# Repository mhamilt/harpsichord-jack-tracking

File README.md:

# Harpsichord Jack Tracking

This repository collects together all materials (CAD Drawings, diagrams, firmware source code) related to Harpsichord Jack Tracking Project at the NEMUS project.

|                              |
| :---------------------------------------------------------: |
| Side View of the model harpsichord used during development. |

- [Harpsichord Jack Tracking](#harpsichord-jack-tracking)
  - [Measurements](#measurements)
    - [Model Keyboard](#model-keyboard)
    - [Jack Pitch](#jack-pitch)
    - [Full Scale Keyboard](#full-scale-keyboard)
    - [Jack Pitch](#jack-pitch-1)
    - [Jack Travel](#jack-travel)
    - [PCB](#pcb)
      - [7 Sensor Face Board](#7-sensor-face-board)
        - [Notes](#notes)
        - [Eagle commands](#eagle-commands)
    - [Gradient Tag](#gradient-tag)
    - [Diagram](#diagram)
  - [QRE1113 Notes](#qre1113-notes)
    - [Spacing](#spacing)
    - [Functionality](#functionality)
    - [Data sheets](#data-sheets)
    - [Multiplexing](#multiplexing)
      - [1. Using 2 Micro controllers](#1-using-2-micro-controllers)
  - [MIDI Specifications](#midi-specifications)
    - [Jack Differentiation](#jack-differentiation)
    - [Aftertouch](#aftertouch)

## Measurements

### Model Keyboard

###  Jack Pitch

| Jack | Centre distance from backboard (mm) |
| ---- | ----------------------------------- |
| 1    | `10.25`                             |
| 2    | `25.1`                              |
| 3    | `38.5`                              |

Gives a rough jack pitch of `14.4875 mm` with an offset of `10.25 mm`.

Pitch of the back row of jacks was determined by measuring from the open edge of the model to the front edge of the jack. Each jack had its width measured providing the values in the table below.

| Jack | Front edge dist (mm) | Width (mm) | Centre dist (mm) |
| ---- | -------------------- | ---------- | ---------------- |
| 4    | `59.85`              | `4.25`     | `61.975`         |
| 5    | `45.25`              | `4.30`     | `47.400`         |
| 6    | `31.20`              | `4.60`     | `33.500`         |

Give a rough pitch of `14.2375 mm` with an offset of  `33.5 mm` from the front edge

### Full Scale Keyboard 

|        |
| :-----------------------------: |
| Top view of the 49-key keyboard |ll

The full scale version of the interface has 49 keys and 2 jack rows. The jacks are generally around `4.65 mm`.

###  Jack Pitch

There is not much variation in the pitch of the jacks. On average the centre-to-centre is `14.02 mm`. Likely error between jacks would compound across the full length. This should be compensated for by the separate pcbs which have groups of 7 sensors.

Space between the jacks is `9.75 mm`, meaning central pcbs will have to have less than half this distance (`4.875mm`) in order to slot together.

###  Jack Travel

The jacks have a height of `91.65mm`. Front jacks have a travel of about `8.5mm` and back jacks `9.0mm` between key release and full key press.

### PCB

With a pitch of `14.02 mm` a theoretical limit to the width of a 7-sensor PCB would be `98.2 mm`, but with margin required from traces this is not possible. The upper limit is `112.22 mm` but with variation during fabrication it is unwise to push the tolerance to the nearest `1/10 mm`. A `1.5 mm` tolerance brings the limit to about `99.7 mm` to `110.7 mm`

#### 7 Sensor Face Board

Face boards mount the QRE1113s perpendicular to the board so that there is no need to bend the through hole mounting legs during assembly.

There are a couple of designs, at at present what is most important is the hole mounts at (`18.00mm`, `10.00mm`) and (`18.00mm`, `81.40mm`)

##### Notes

##### Eagle commands

```py
ox = 1.71     # min distance from board edge
pitch = 14.02 # jack pitch
[(x * pitch) + ox for x in range(0,7)]
[1.71, 15.73, 29.75, 43.77, 57.79, 71.80999999999999, 85.83]
```

Python can be used to automatically generate the placement of all pieces.

```py
qrepitch = 1.8 # placement is calculated from the #1 pin, pitch is used to offset to the centre
ox = 1.71     # min distance from board edge
oy = 1.71     # min distance from board edge in y axis
pitch = 14.02 # jack pitch
max_board_width = (6*pitch) + ox + qrepitch + ox

for index, point in enumerate([(x * pitch) + ox for x in range(0,7)]):
  print(f"move Q{index+1} ({oy} {point});")
  # print(f"rotate Q{index+1};")
for index, point in enumerate([(x * pitch) + ox for x in range(0,16)]):
  print(f"move Q{index+1} ({oy} {point});")

# Ideal LED placement
for index, point in enumerate([(x * pitch) + ox for x in range(0,7)]):
  print(f"move D{index+1} ({23.8} {point+qrepitch/2});")

resitor10k_ox = 10.1 # min distance from board edge in y axis
resitor10k_oy = 7.0 # min distance from board edge in y axis
resitor100_ox = 7.5 # min distance from board edge in y axis
resitor100_oy = 7.0 # min distance from board edge in y axis
rpitch = 12.9

for index, point in enumerate([(x * rpitch) + resitor100_oy for x in range(0,16)]):
  if index < 7:
    print(f"move R{(index*2)+1} ({resitor100_ox} {point});")
    print(f"move R{(index+1)*2} ({resitor10k_ox} {point});")
  if index >= 7:
    print(f"move R{((index+1)*2)+1} ({resitor100_ox} {point});")
    print(f"move R{((index+1)+1)*2} ({resitor10k_ox} {point});")

for index, point in enumerate([(x * 12.6) + 7 for x in range(0,7)]):
  print(f"move LED{(index+1)} (34 {point});")

for index, point in enumerate([(x * 12.) + 7 for x in range(0,7)]):
  print(f"rotate LED{(index+1)};")

for index, point in enumerate([(x * 12.6) + 7 for x in range(17,34)]):
  print(f"rotate R{(index+17)};")

for index, point in enumerate([(x * 12.6) + 7 for x in range(0,7)]):
  print(f"rotate R{(index+15)};")
  print(f"move R{(index+15)} (30 {point});")

for index, point in enumerate([(x * 2.6) + 41 for x in range(0,16)]):  
  print(f"move R{(index+15)} (18 {point});")

for index, point in enumerate([(x * 12.6) + 7 for x in range(0,7)]):
  print(f"rotate R{(index+15)};")

for index, point in enumerate([(x * 12.6) + 7 for x in range(0,7)]):
  print(f"mirror R{(index+15)};")

for index, point in enumerate([(x * 12.) + 7 for x in range(0,7)]):
  print(f"mirror LED{(index+1)};")

led_ox = 33 # min distance from board edge in y axis
led_oy = 9 # min distance from board edge in y axis

for index, point in enumerate([(x * 12.) + led_ox for x in range(0,7)]):
  print(f"rotate D{(index+1)};")
  print(f"rotate D{(index+1)};")

for index, point in enumerate([(x * 12.) + led_ox for x in range(0,7)]):
  print(f"rotate D{(index+1)};")
  print(f"move D{(index+1)} ({led_ox} {point});")
  print(f"mirror D{(index+1)};")

for index, point in enumerate([(x * 13) + led_oy for x in range(0,16)]):
  print(f"move D{(index+1)} ({led_ox} {point});")

for index, point in enumerate([(x * 12.) + led_ox for x in range(0,16)]):
  print(f"rotate D{(index+7)};")
  print(f"move D{(index+7)} ({led_ox} {point});")
  print(f"mirror D{(index+7)};")

for index, point in enumerate([(x * 12.) + led_oy for x in range(0,7)]):  
  print(f"move D{(index+1)} ({led_ox} {point});")
  
```

### Gradient Tag

The QRE1113 reflects from a tag with a gradient printed.

The should be `40 mm` in length to avoid potential catching on the jack hole. The active area of the gradient need only be the length of the [jack travel](#jack-travel)

### Diagram

|                 |
| :-----------------------------------------------: |
| Cross-section of full sized harpsichord interface |

## QRE1113 Notes

|              |
| :---------------------------------------------------------: |
| Model keyboard and QRE1113s attached to Arduino Nano 33 IoT |

Displacement of the jacks is measure using QRE1113 IR LED / Transistor pair. The section covers some general observations and helpful information about these sensors.

### Spacing

Distance between pins is `1.8mm` meaning the space from the centre is `0.9mm`. CAD placement should offset by `0.9mm` to compensate.

|                 |         |
| --------------- | ------- |
| short leg pitch | `1.80mm` |
| long leg pitch  | `3.80mm` |

### Functionality

QRE1113s are used with alongside adhesive strips with a black and white gradient printed on it, which are attached to each jack. 

The optimal distance between the strip and the sensor is around 6mm with a voltage reference of [`1.65V` provided by Arduino SAMD boards](https://www.arduino.cc/reference/en/language/functions/analog-io/analogreference/)

|  |
| :-----------------------------------------: |
|     Jacks with gradient strip attached      |

### Data sheets

- [QRE1113 Datasheet](https://www.mouser.in/datasheet/2/308/QRE1113-1121523.pdf)

|  |  |
| :----------------------------------------------------------------------------------------------------------------------------------------: | :----------------------------------------------------------------------------------------------------------------------------------------: |
|                     QRE1113 Dimension. Not that pin 1 should always have a chamfer on the corner to help identify it.                      |                                                               QRE1113 Pinout                                                               |

### Multiplexing

- 14 Boards
- 7 sensors each
- 7 analog channels
- 8 channel multiplexer

- BLE Nano
  - 8 ADC channels A0 - A7
  - For 8 ADC channels an 8-channel multiplexer will allow for 8 boards to address 8 sensors.

Solutions:

1. Use 2 micro controllers, one for front, one for back
  - each a separate MIDI device
2. cascade front and back
  1. two groups of transistors
      - 16 transistors
        - 2 sets of 7 for signals
        - 2 extra for interfacing with the others
      - 2 extra digital pins used
  2. another bank of multiplexers
      - 7 multiplexers for groups of seven boards
      - 3 more digital pins for control 

#### 1. Using 2 Micro controllers

- Each sensor board needs 8 pins
  
  1. GND 
  2. VCC/VDD 5V
  3. VDD 3V
  4. Mux Address A
  5. Mux Address B
  6. Mux Address C
  7. LED Data
  8.  Signal 1
  9.  Signal 2
  10. Signal 3
  11. Signal 4
  12. Signal 5
  13. Signal 6
  14. Signal 7

## MIDI Specifications

Below are additional MIDI specifications retrieve the most information from the controller. 

Currently this is being written and subject to change

### Jack Differentiation

There is one channel per key as per [Standard MPE specifications](https://midi.org/mpe-midi-polyphonic-expression#:~:text=The%20MPE%20specification%20defines%20a,products%2C%20using%20MIDI%201.0%20messages.).

There are two note ons with associated velocities and note offs

A `note on` message `channel`, `pitch value`, `velocity`.

Velocity demarcates wether the note on message is related to the first jack or the second jack.

Given the signal obtained from the jack tracking does not provide the resolution in velocity to utilize the full 7 bit set of velocity values.

The First jack uses the velocity values from `0` to `63` and the second jack from `64` to `127`.

Note off messages use the same specification.

Therefore the physical model can relate the note off message to it's respective note on message.

example:

|            | Jack1 | Jack2  |
| ---------- | ----- | ------ |
| `channel`  | 1     | 1      |
| `pitch`    | 56    | 56     |
| `velocity` | 0-63  | 64-127 |

**NOTE:** There is a secondary use case where the controller is used with a digital instrument that expects a standard MPE signal. In that case there _may_ be problem. However, it is not guaranteed to not work. Behavior in this case is undefined.

The same is true of the plug-in, which will be written to expect the above format of note messages.
As a result, the plug-in will need two modes of operation. A standard MPE for using with a standard MPE keyboard requiring a single note on/note off per key. The second mode designed specifically for the harpsichord keyboard interface. This gives control of the excitation of both of the strings.

### Aftertouch

Channel Pressure (MIDI Status event nybble `0xD`) is sent as one stream, taken from the front jack tracking signal.

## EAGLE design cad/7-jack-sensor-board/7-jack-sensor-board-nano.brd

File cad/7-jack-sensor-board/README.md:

# 7 Jack Sensor Board

This word was an intermediate to try out the new spacing for the full scale model

Pins for an Arduino Nano are included directly on the board.

## Wiring

|   Connection   | Pin |
| -------------- | --- |
| Jack 0 QRE1113 | A0  |
| Jack 1 QRE1113 | A1  |
| Jack 2 QRE1113 | A2  |
| Jack 3 QRE1113 | A3  |
| Jack 4 QRE1113 | A4  |
| Jack 5 QRE1113 | A6  |
| Jack 6 QRE1113 | A7  |
| Jack 0 LED     | D3  |
| Jack 1 LED     | D4  |
| Jack 2 LED     | D5  |
| Jack 3 LED     | D6  |
| Jack 4 LED     | D7  |
| Jack 5 LED     | D8  |
| Jack 6 LED     | D9  |
| Rotary CLK     | D12 |
| Rotary DATA    | D11 |
| Rotary Switch  | D10 |

## PCB

### Eagle Libraries

- https://github.com/cyberlink1/Arduino-Eagle-Cad-Library

### Logo

[Imagemagick](https://imagemagick.org) was use to quantise the nemus logo to a 1-bit bitmap for the silkscreen

```sh
magick logo.png logo.bmp
magick logo.bmp -resize 8x8% logo.bmp
magick logo.bmp -monochrome logo.bmp
magick -flop -flip logo.bmp logo_b.bmp # for the bottom layer, the image is reversed
```

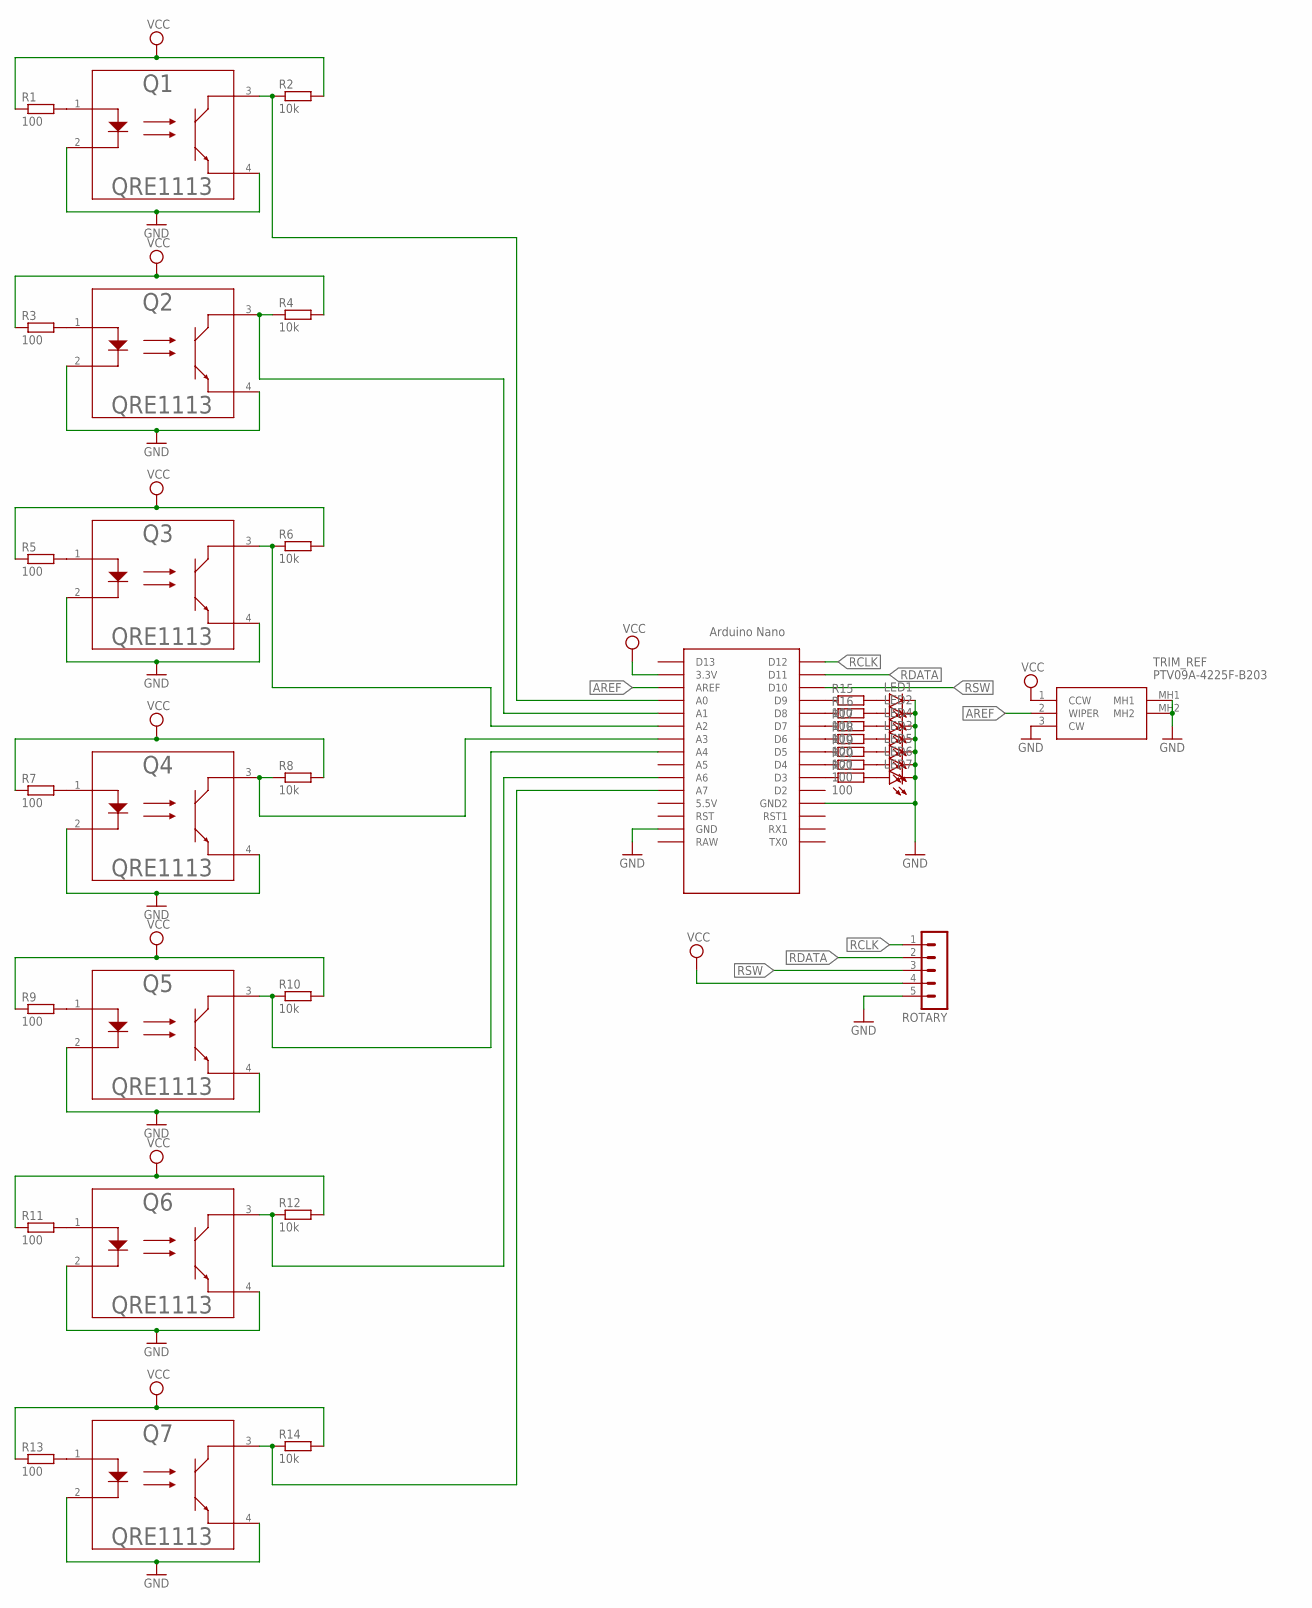
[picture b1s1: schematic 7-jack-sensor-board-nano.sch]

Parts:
LED1, LED2, LED3, LED4, LED5, LED6, LED7: LED3MM
Q1, Q2, Q3, Q4, Q5, Q6, Q7: QRE1113; DIP4_100AQ_ONS
R1, R3, R5, R7, R9, R11, R13, R15, R16, R17, R18, R19, R20, R21: 100; 0207/10
R2, R4, R6, R8, R10, R12, R14: 10k; 0207/10
ROTARY: MA05-1
TRIM_REF: PTV09A-4225F-B203; PTV09A4225FB203
U$1: NANO

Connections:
AREF: TRIM_REF.2 (WIPER), U$1.AREF
GND: LED1.K (C), LED2.K (C), LED3.K (C), LED4.K (C), LED5.K (C), LED6.K (C), LED7.K (C), Q1.2, Q1.4, Q2.2, Q2.4, Q3.2, Q3.4, Q4.2, Q4.4, Q5.2, Q5.4, Q6.2, Q6.4, Q7.2, Q7.4, ROTARY.5, TRIM_REF.3 (CW), TRIM_REF.MH1, TRIM_REF.MH2, U$1.GND, U$1.GND1 (GND2)
unnamed: Q1.1, R1.2
unnamed: Q1.3, R2.1, U$1.A0
unnamed: Q2.1, R3.2
unnamed: Q2.3, R4.1, U$1.A1
unnamed: Q3.1, R5.2
unnamed: Q3.3, R6.1, U$1.A2
unnamed: Q4.1, R7.2
unnamed: Q4.3, R8.1, U$1.A3
unnamed: Q5.1, R9.2
unnamed: Q5.3, R10.1, U$1.A4
unnamed: Q6.1, R11.2
unnamed: Q6.3, R12.1, U$1.A6
unnamed: Q7.1, R13.2
unnamed: Q7.3, R14.1, U$1.A7
unnamed: R15.1, U$1.D9
unnamed: R16.1, U$1.D8
unnamed: R17.1, U$1.D7
unnamed: R18.1, U$1.D6
unnamed: R19.1, U$1.D5
unnamed: R20.1, U$1.D4
unnamed: R21.1, U$1.D3
unnamed: LED1.A, R15.2
unnamed: LED2.A, R16.2
unnamed: LED3.A, R18.2
unnamed: LED4.A, R17.2
unnamed: LED5.A, R19.2
unnamed: LED6.A, R20.2
unnamed: LED7.A, R21.2
RCLK: ROTARY.1, U$1.D12
RDATA: ROTARY.2, U$1.D11
RSW: ROTARY.3, U$1.D10
VCC: R1.1, R2.2, R3.1, R4.2, R5.1, R6.2, R7.1, R8.2, R9.1, R10.2, R11.1, R12.2, R13.1, R14.2, ROTARY.4, TRIM_REF.1 (CCW), U$1.3.3V

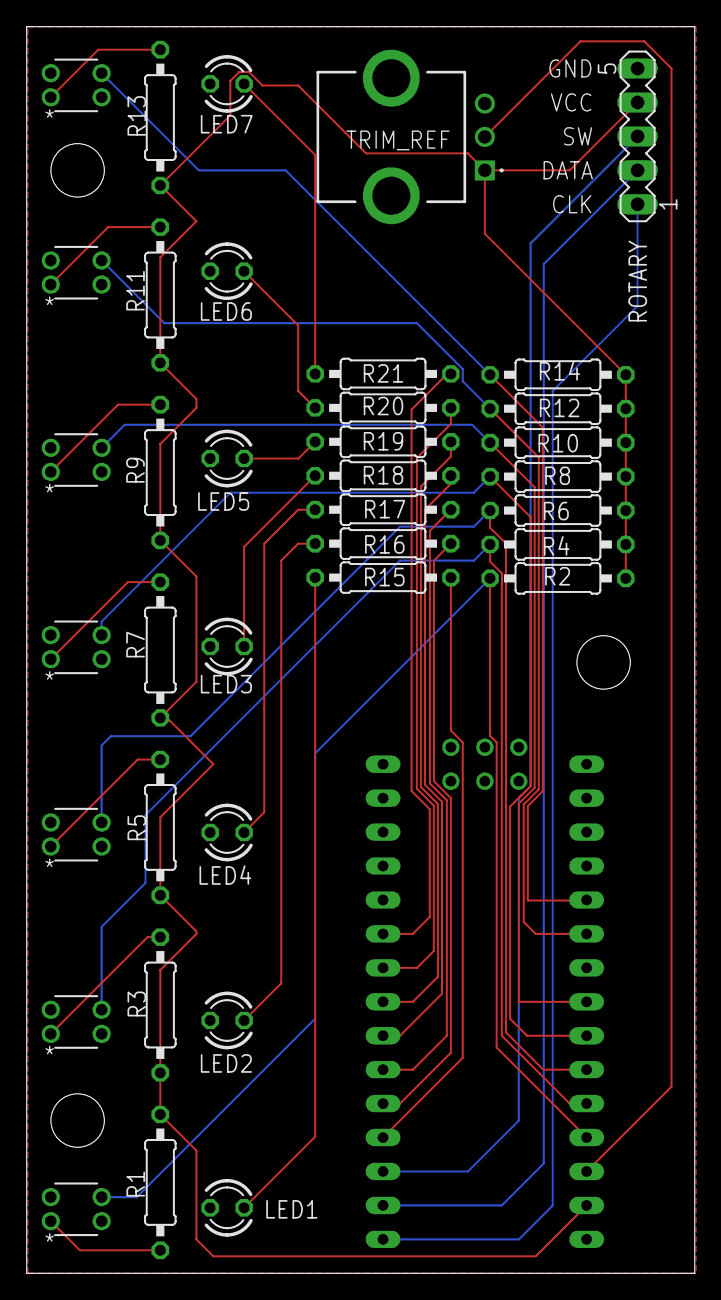
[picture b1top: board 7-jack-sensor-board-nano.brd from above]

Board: 2 copper layers, 50.0 x 93.3 mm, 38 parts (0 on the bottom side), 34 nets.

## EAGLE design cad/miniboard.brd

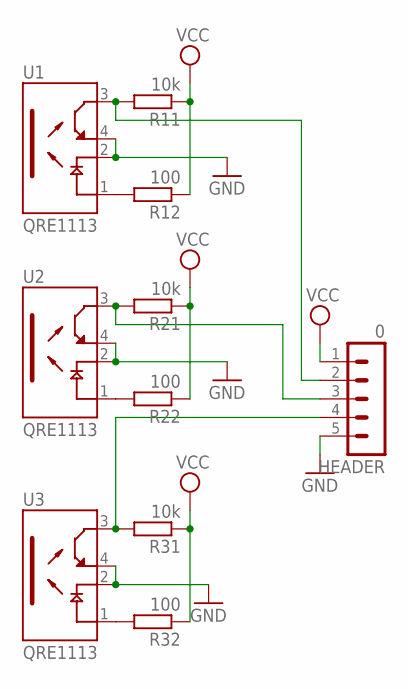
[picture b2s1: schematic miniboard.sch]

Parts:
HEADER: 0; MA05-1
R11, R21, R31: 10k; 0207/10
R12, R22, R32: 100; 0207/10
U1, U2, U3: QRE1113; DIP400W50P180L360H200Q4

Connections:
GND: HEADER.5, U1.2 (C), U1.4 (ET), U2.2 (C), U2.4 (ET), U3.2 (C), U3.4 (ET)
unnamed: HEADER.4, R31.2, U3.3 (CT)
unnamed: HEADER.2, R11.2, U1.3 (CT)
unnamed: R32.2, U3.1 (A)
unnamed: R22.2, U2.1 (A)
unnamed: HEADER.3, R21.2, U2.3 (CT)
unnamed: R12.2, U1.1 (A)
VCC: HEADER.1, R11.1, R12.1, R21.1, R22.1, R31.1, R32.1

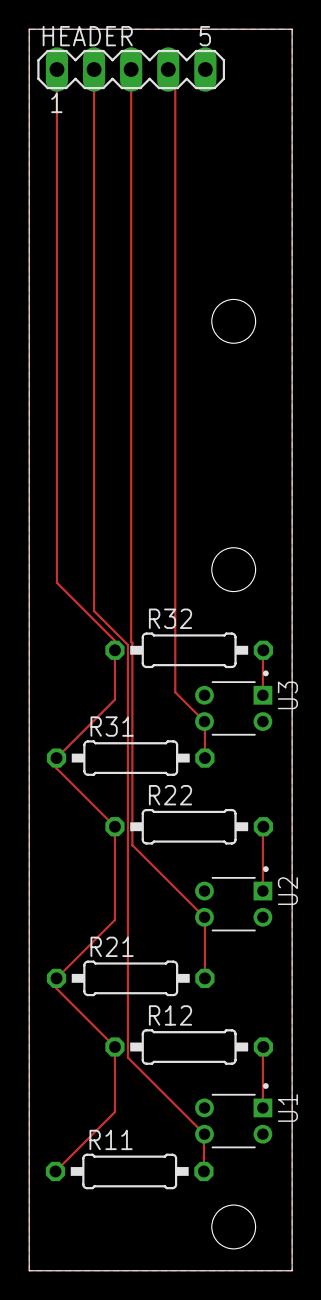
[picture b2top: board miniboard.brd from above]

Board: 2 copper layers, 18.0 x 85.0 mm, 10 parts (0 on the bottom side), 8 nets.

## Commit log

2024-02-05 add images
2024-06-04 init
2024-06-07 add debug design sketches
2024-06-10 move threshold editing to debug mode
2024-06-10 add first-run tag for eeprom data
2024-06-11 intergrate debug mode into main sketch
2024-06-12 add: 6 jack version
2024-06-13 add wiring table
2024-06-17 add aftertouch function
2024-06-17 rename images
2024-06-17 add cad files
2024-06-17 expand readme
2024-06-17 centre table images
2024-07-01 add 49-key keyboard images
2024-07-04 add cad data for 7-key protoboard
2024-07-15 add note on jack travel
2024-07-16 typo
2024-07-16 add src for 7 note pcb
2024-09-26 logo generation info
2024-09-26 qre images
2024-10-21 add full keyboard firmware src
2024-10-25 re-init full model firmware
2024-10-25 add pinout
2024-10-25 add jack state enums
2024-10-25 add index note mapping
2024-10-31 debug mode for fitting in san colombano
2024-11-01 transpose lowest note to C2
2024-11-01 add standard mode leds
2024-11-02 fix eeprom read bug
2024-11-06 add printing again
2024-11-06 remove old cad
2024-11-06 add cad as submodule
2024-11-06 remove old scripts
2024-11-06 add `PluggableUSBMIDI` for nano BLE
2025-03-26 add data logging scripts
2025-03-26 add esp-idf tests
2025-03-26 add component tests

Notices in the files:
parts and their libraries:
COPYRIGHT: Copyright (C) 2024 Ultra Librarian. All rights reserved.
